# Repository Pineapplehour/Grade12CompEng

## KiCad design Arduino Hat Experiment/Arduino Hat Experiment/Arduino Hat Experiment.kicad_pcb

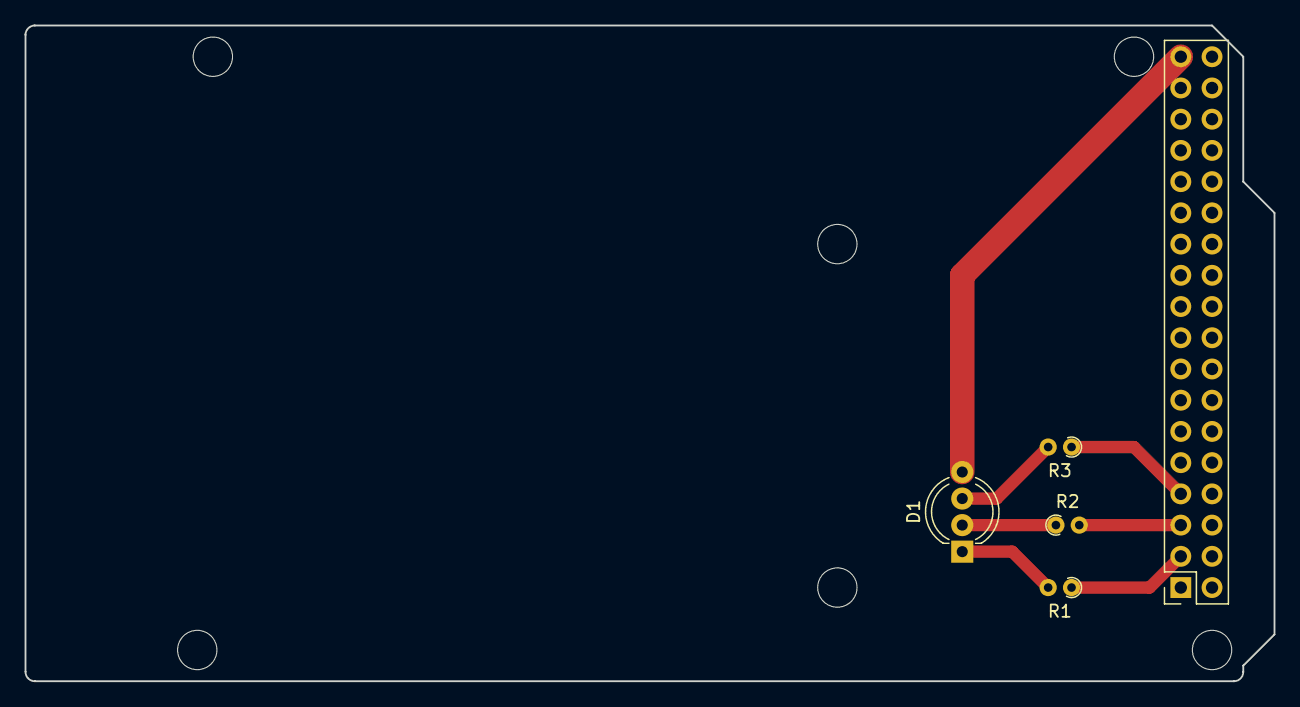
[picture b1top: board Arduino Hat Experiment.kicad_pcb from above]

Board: 2 copper layers, 101.6 x 53.3 mm, 11 parts (0 on the bottom side), 8 nets.

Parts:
D1: LED_RGBA; LED_D5.0mm-4_RGB_Wide_Pins
J7: Digital; PinSocket_2x18_P2.54mm_Vertical
MH1, MH2, MH3, MH4, MH5, MH6: MountingHole_3.2mm
R1, R2, R3: R; R_Axial_DIN0204_L3.6mm_D1.6mm_P1.90mm_Vertical

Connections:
+5V: D1.4 (A), J7.35, J7.36
/48: J7.7, R3.1
/50: J7.5, R2.2
/*52: J7.3, R1.1
GND: J7.1, J7.2
unnamed: D1.3 (BK), R3.2
unnamed: D1.2 (GK), R2.1
unnamed: D1.1 (RK), R1.2

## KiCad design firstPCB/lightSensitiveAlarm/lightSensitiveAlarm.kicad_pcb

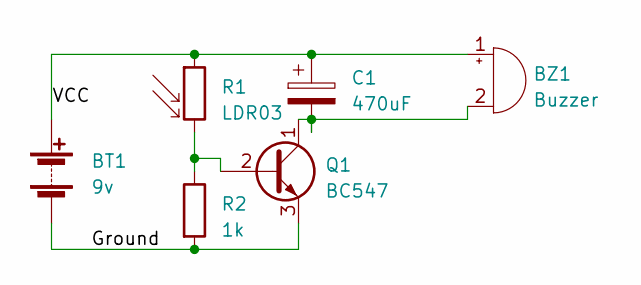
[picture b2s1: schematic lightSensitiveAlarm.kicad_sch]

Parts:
BT1: 9v; PinHeader_1x02_P2.54mm_Vertical
BZ1: Buzzer; Buzzer_12x9.5RM7.6
C1: 470uF; CP_Radial_D10.0mm_P5.00mm
Q1: BC547; TO-92_Inline
R1: LDR03; R_LDR_10x8.5mm_P7.6mm_Vertical
R2: 1k; R_Axial_DIN0414_L11.9mm_D4.5mm_P15.24mm_Horizontal

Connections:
/Ground: BT1.2 (-), Q1.3 (E), R2.2
/VCC: BT1.1 (+), BZ1.1 (-), C1.1, R1.1
unnamed: BZ1.2 (+), C1.2, Q1.1 (C)
unnamed: Q1.2 (B), R1.2, R2.1

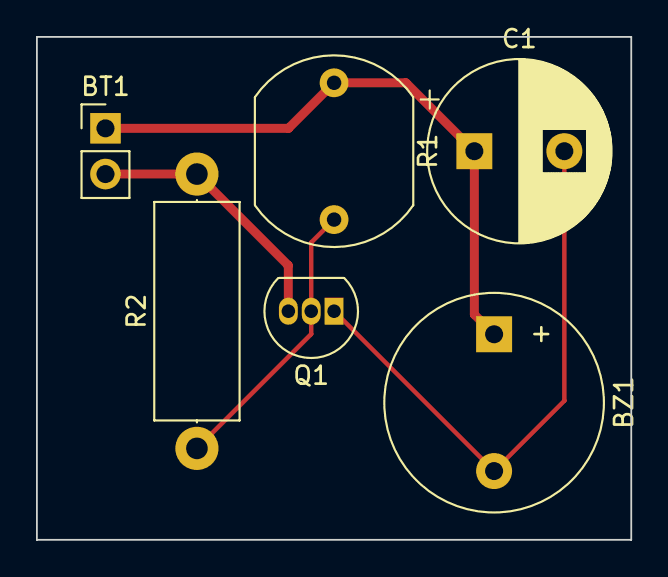
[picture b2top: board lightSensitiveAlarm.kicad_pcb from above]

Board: 2 copper layers, 33.0 x 27.9 mm, 6 parts (0 on the bottom side), 4 nets.

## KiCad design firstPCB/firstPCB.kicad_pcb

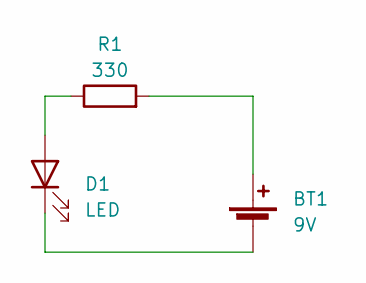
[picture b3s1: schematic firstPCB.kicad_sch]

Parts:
BT1: 9V; BatteryHolder_Bulgin_BX0036_1xC
D1: LED; LED_D5.0mm
R1: 330; R_Axial_DIN0204_L3.6mm_D1.6mm_P5.08mm_Horizontal

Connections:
unnamed: BT1.1 (+), R1.2
unnamed: BT1.2 (-), D1.1 (K)
unnamed: D1.2 (A), R1.1

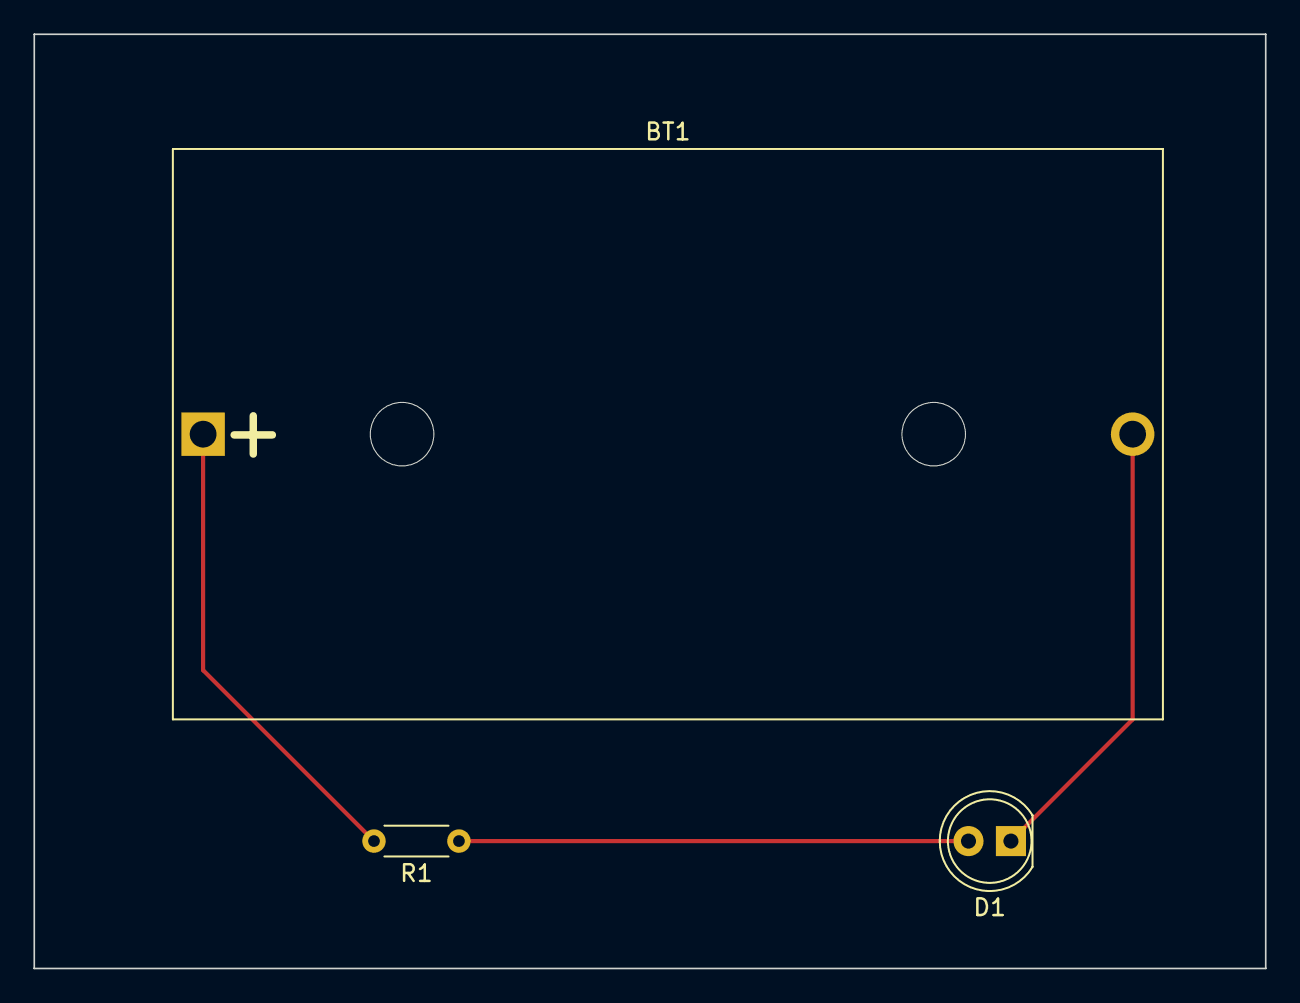
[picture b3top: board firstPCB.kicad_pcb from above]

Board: 2 copper layers, 73.7 x 55.9 mm, 3 parts (0 on the bottom side), 3 nets.

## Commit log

2023-03-10 PUSHING P
2023-03-21 Its fixed
2023-03-21 New Stuff
2023-03-22 what
2023-03-23 good stuff
2023-04-20 freshing it up
2023-04-21 newer
2023-04-21 done
2023-04-21 rename
2023-04-25 jazz
2023-04-26 mmmmmhm
2023-04-27 CHeee
